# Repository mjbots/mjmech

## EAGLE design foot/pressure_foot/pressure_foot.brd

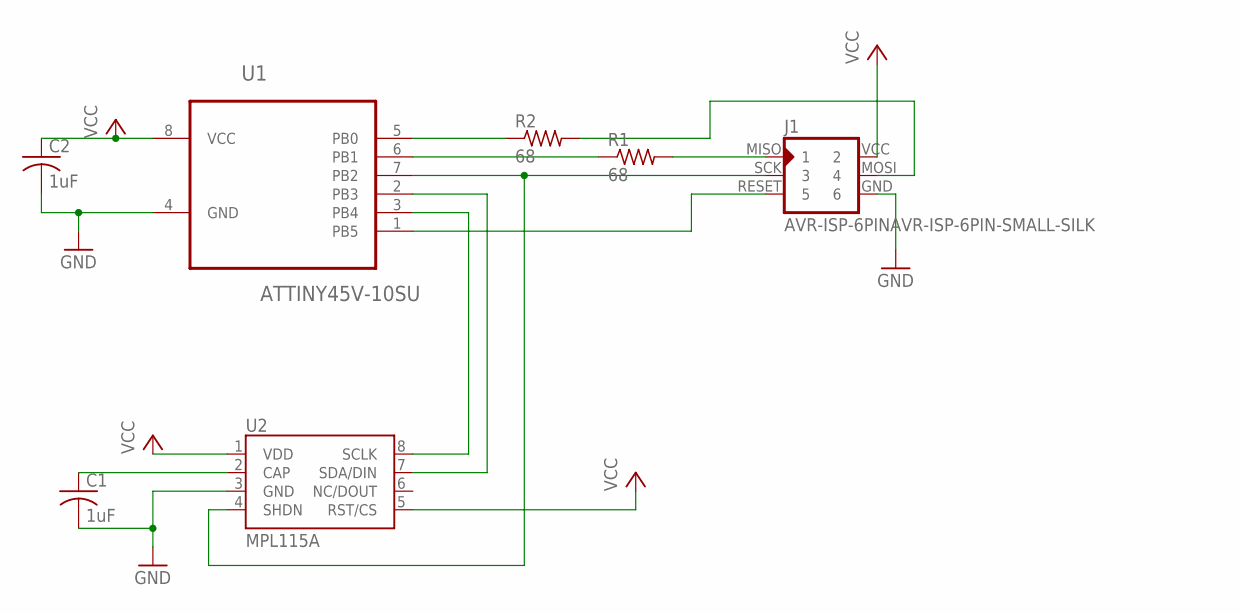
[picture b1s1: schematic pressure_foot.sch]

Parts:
C1, C2: 1uF; C0603
J1: AVR-ISP-6PINAVR-ISP-6PIN-SMALL-SILK; AVR-ISP-6PIN-SMAILL-SILK
R1, R2: 68; R0603
U1: ATTINY45V-10SU; SOIC127P798X216-8N
U2: MPL115A; LGA8

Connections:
GND: C1.2, C2.2, J1.GND (6), U1.4 (GND), U2.3 (GND)
unnamed: J1.RESET (5), U1.1 (PB5)
unnamed: J1.MISO (1), R1.2
unnamed: R2.1, U1.5 (PB0)
unnamed: R1.1, U1.6 (PB1)
unnamed: J1.MOSI (4), R2.2
unnamed: C1.1, U2.2 (CAP)
unnamed: U1.3 (PB4), U2.8 (SCLK)
unnamed: U1.2 (PB3), U2.7 (SDA/DIN)
unnamed: J1.SCK (3), U1.7 (PB2), U2.4 (SHDN)
VCC: C2.1, J1.VCC (2), U1.8 (VCC), U2.1 (VDD), U2.5 (RST/CS)

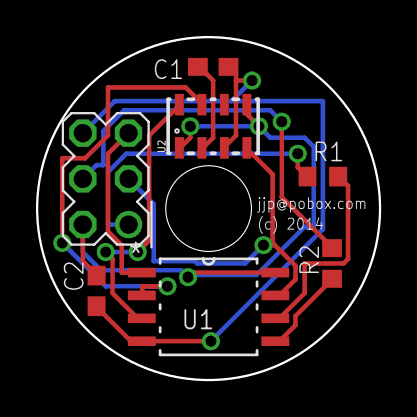
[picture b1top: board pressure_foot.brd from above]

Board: 2 copper layers, 19.0 x 19.0 mm, 7 parts (0 on the bottom side), 11 nets.

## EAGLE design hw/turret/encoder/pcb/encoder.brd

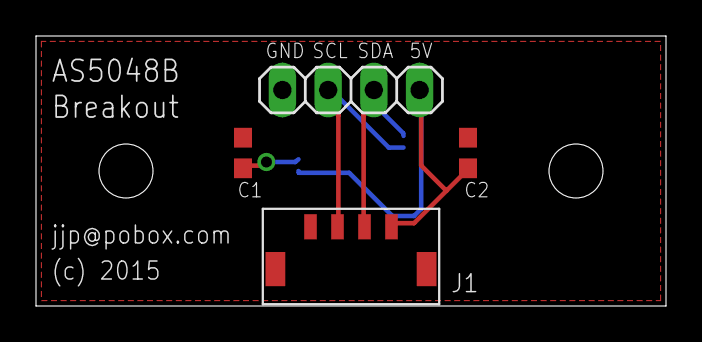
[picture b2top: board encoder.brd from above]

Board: 2 copper layers, 35.0 x 15.0 mm, 5 parts (1 on the bottom side), 5 nets.

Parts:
C1: 10uF; C0603
C2: 100nF; C0603
J1: JST-ZH4ZH4-RA; JST_ZH4_RA
JP1: 1X04
U1: AS5048BTSSOP14; TSSOP14

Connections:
GND: C1.2, C2.2, J1.1, JP1.1, U1.3, U1.4, U1.13
unnamed: C1.1, U1.12
unnamed: J1.2, JP1.2, U1.2
unnamed: J1.3, JP1.3, U1.1
VCC: C2.1, J1.4, JP1.4, U1.11

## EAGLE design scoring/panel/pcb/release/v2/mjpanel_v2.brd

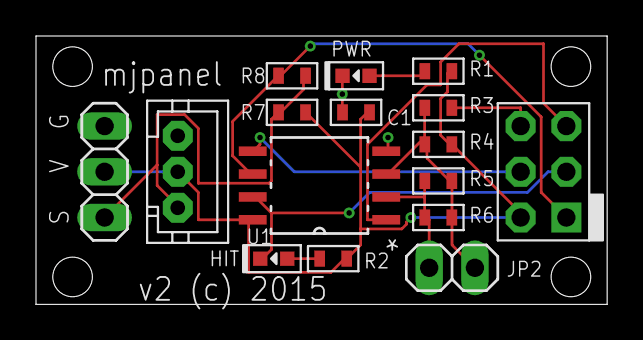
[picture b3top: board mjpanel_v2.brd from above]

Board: 2 copper layers, 31.7 x 14.9 mm, 16 parts (0 on the bottom side), 11 nets.

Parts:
C1: 1uF; C0603
HIT: GRN; LED0603
J1: AVRISP6_COMPACT; CON6P2R
JP1: 1X03
JP2: 1X02
PWR: RED; LED0603
R1, R2: 560; R0603
R3, R4: 10k; R0603
R5: DNP; R0603
R6: 100; R0603
R7: 2k; R0603
R8: 47; R0603
U1: ATTINY85-20SU; SOIC127P798X216-8N
U$1: JST-PH3

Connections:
GND: C1.P$2, J1.6, JP1.3, PWR.CATHODE, R3.P$1, U1.4, U$1.3
unnamed: PWR.ANODE, R1.P$1
unnamed: J1.5, U1.1
unnamed: JP2.2, R3.P$2, R4.P$2, R5.P$1, R6.P$1, U1.3
unnamed: HIT.CATHODE, J1.3, U1.7
unnamed: HIT.ANODE, R2.P$1
unnamed: JP2.1, R5.P$2, R6.P$2, U1.2
unnamed: J1.4, U1.5
unnamed: JP1.1, R7.P$1, R8.P$2, U$1.1
unnamed: J1.1, R8.P$1, U1.6
VCC: C1.P$1, J1.2, JP1.2, R1.P$2, R2.P$2, R4.P$1, R7.P$2, U1.8, U$1.2

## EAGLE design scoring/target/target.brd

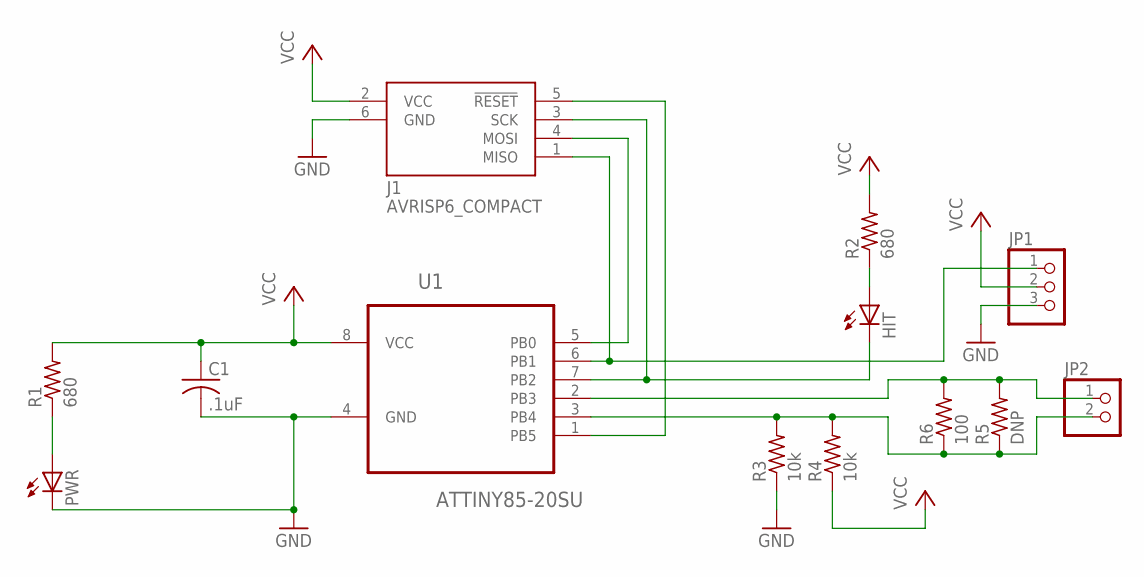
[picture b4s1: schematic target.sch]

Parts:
C1: .1uF; C0805
HIT: LEDSML0805; SML0805
J1: AVRISP6_COMPACT; CON6P2R
JP1: PINHD-1X3; 1X03
JP2: PINHD-1X2; 1X02
PWR: LEDSML0805; SML0805
R1, R2: 680; R0805
R3, R4: 10k; R0805
R5: DNP; R0805
R6: 100; R0805
U1: ATTINY85-20SU; SOIC127P798X216-8N

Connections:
GND: C1.2, J1.6 (GND), JP1.3, PWR.C, R3.1, U1.4 (GND)
unnamed: PWR.A, R1.1
unnamed: J1.5 (!RESET), U1.1 (PB5)
unnamed: JP2.2, R3.2, R4.2, R5.1, R6.1, U1.3 (PB4)
unnamed: HIT.C, J1.3 (SCK), U1.7 (PB2)
unnamed: HIT.A, R2.1
unnamed: JP2.1, R5.2, R6.2, U1.2 (PB3)
unnamed: J1.4 (MOSI), U1.5 (PB0)
unnamed: J1.1 (MISO), JP1.1, U1.6 (PB1)
VCC: C1.1, J1.2 (VCC), JP1.2, R1.2, R2.2, R4.1, U1.8 (VCC)

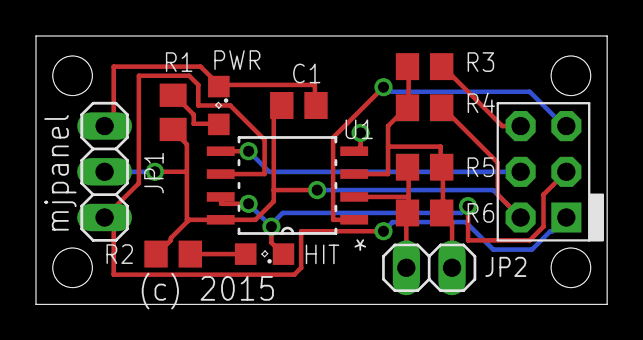
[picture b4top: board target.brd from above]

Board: 2 copper layers, 31.7 x 14.9 mm, 13 parts (0 on the bottom side), 10 nets.

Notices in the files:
foot/pressure_foot/pressure_foot.brd:
(c) 2014
hw/turret/encoder/pcb/encoder.brd:
(c) 2015
scoring/panel/pcb/release/v2/mjpanel_v2.brd:
v2 (c) 2015
parts and their libraries:
SparkFun-Sensors: Licensing: Creative Commons ShareAlike 4.0 International - https://creativecommons.org/licenses/by-sa/4.0
